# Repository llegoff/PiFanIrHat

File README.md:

[:fr:](LISEZMOI.md) [:uk:](README.md)

buy rev1 on [ebay](https://www.ebay.fr/itm/153597547428) :package:

buy rev1 (silent fan) on [ebay](https://www.ebay.fr/itm/153600642463) :package:

# PiFanIrHat

### Fan

:warning: need raspbian buster, good version of gpio-fan overlay, come with kernel 4.19.

configuration: edit /boot/config.txt, add folowing line

    dtoverlay=gpio-fan,gpiopin=18,temp=55000

### On/Off button

on/off button is connected to gpio3 and GND

configuration: edit /boot/config.txt, add folowing line

    dtoverlay=gpio-shutdown,gpio_pin=3,active_low=1,gpio_pull=up
    
:warning: on raspberry pi 4, only shutdown work, with original bootloader. For power on, bootloader need to be update to ~~RC3.3~~ last version (see https://www.raspberrypi.org/forums/viewtopic.php?f=117&t=246027)

Download the last bootloader at recovery section https://www.raspberrypi.org/downloads/

### IR receiver

install ir-keytable

    sudo apt install ir-keytable

configuration: edit /boot/config.txt, add folowing line

    dtoverlay=gpio-ir,gpio_pin=17,gpio_pull=1,rc-map-name=<keymap file for your remote>

keymap files path is /lib//udev/rc_keymaps/

test remote

    sudo ir-keytable -t -v -p all

### IR power On

:warning: on raspberry pi 4, only shutdown work, with original bootloader. For power on, bootloader need to be update to ~~RC3.3~~ last version (see https://www.raspberrypi.org/forums/viewtopic.php?f=117&t=246027)

Download the last bootloader at recovery section https://www.raspberrypi.org/downloads/

:grey_exclamation: For key learning, press Rec button, led stay on, press remote key, led return off.

flash Attiny85 with file [PiFanIr.hex](attiny85/PiFanIr.hex?raw=true)

    avrdude -p attiny85 -P COM5 -b 19200 -c avrisp -u -U flash:w:PiFanIr.hex

flash attiny85 fuses : lfuse:E2 , efuse:FF , hfuse:DF

    avrdude -p attiny85 -P COM5 -b 19200 -c avrisp -u -U lfuse:w:0xe2:m -U hfuse:w:0xdf:m -U efuse:w:0xff:m

## PCB

## Schematic

## Révision
rev1
- bad footprint for eeprom

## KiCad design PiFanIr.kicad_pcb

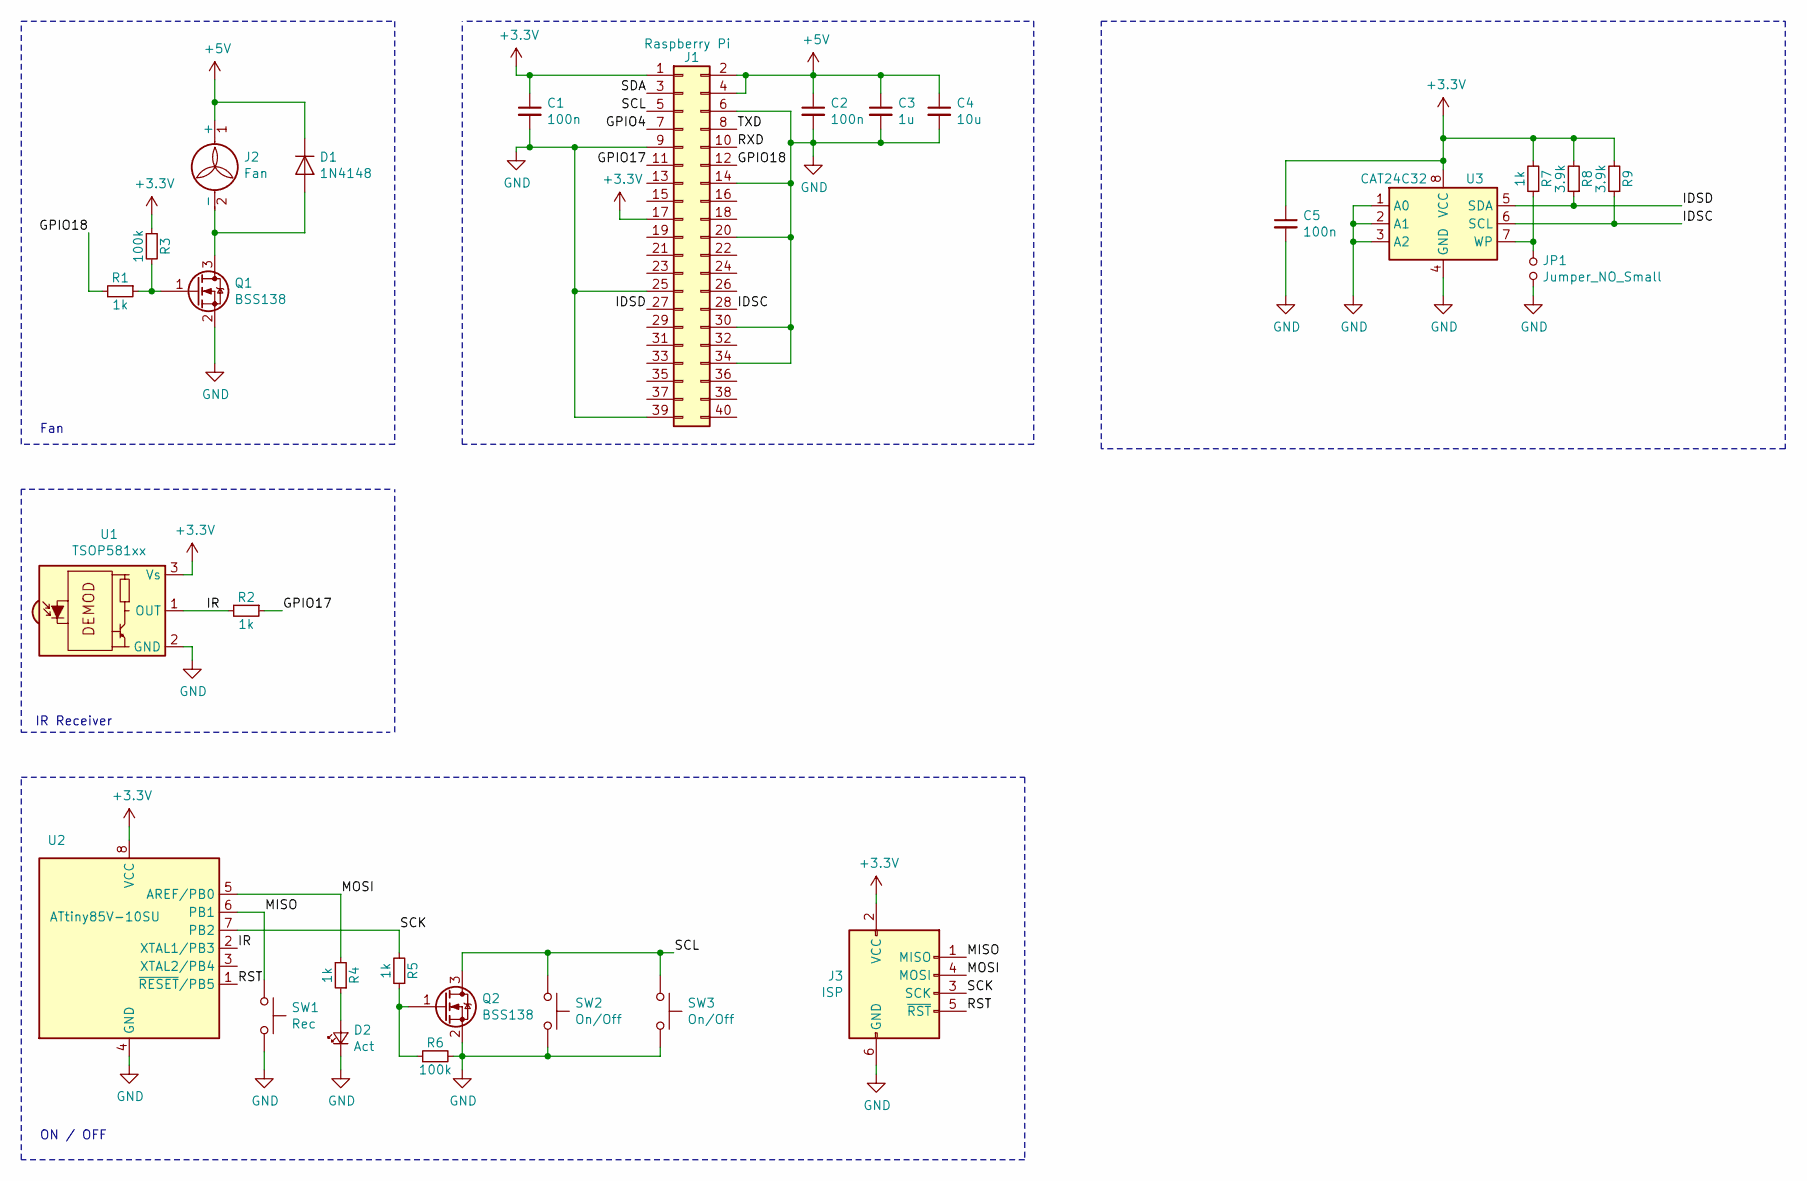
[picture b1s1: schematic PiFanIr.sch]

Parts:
C1, C2, C5: 100n; C_0805
C3: 1u; C_0805
C4: 10u; C_0805
D1: 1N4148; D_SOD-123
D2: Act; LED_0805
J1: Raspberry Pi; RaspberryPiHAT
J2: Fan; Pin_Header_Angled_1x02_Pitch2.54mm
J3: ISP; Pin_Header_Straight_2x03_Pitch2.54mm
JP1: Jumper_NO_Small; Pin_Header_Straight_1x02_Pitch2.54mm
Q1, Q2: BSS138; SOT-23
R1, R2, R4, R5, R7: 1k; R_0805
R3, R6: 100k; R_0805
R8, R9: 3.9k; R_0805
SW1: Rec; SW_SPST_TL3342
SW2: On/Off; SW_Tactile_SPST_Angled_PTS645Vx31-2LFS
SW3: On/Off; SW_SPST_TL3342
U1: TSOP581xx; IRReceiver_Vishay_MINICAST-3pin
U2: ATtiny85V-10SU; SOIJ-8_5.3x5.3mm_Pitch1.27mm
U3: CAT24C32; SOIJ-8_5.3x5.3mm_Pitch1.27mm

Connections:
+3V3: C1.1, C5.1, J1.1, J1.17, J3.2 (VCC), R3.1, R7.2, R8.2, R9.2, U1.3 (Vs), U2.8 (VCC), U3.8 (VCC)
+5V: C2.1, C3.1, C4.1, D1.1 (K), J1.2, J1.4, J2.1 (+)
/GPIO4: J1.7
/GPIO17: J1.11, R2.1
/GPIO18: J1.12, R1.2
/IDSC: J1.28, R9.1, U3.6 (SCL)
/IDSD: J1.27, R8.1, U3.5 (SDA)
/IR: R2.2, U1.1 (OUT), U2.2 (XTAL1/PB3)
/MISO: J3.1 (MISO), SW1.1, U2.6 (PB1)
/MOSI: J3.4 (MOSI), R4.2, U2.5 (AREF/PB0)
/RST: J3.5 (~RST), U2.1 (~RESET~/PB5)
/RXD: J1.10
/SCK: J3.3 (SCK), R5.2, U2.7 (PB2)
/SCL: J1.5, Q2.3 (D), SW2.1, SW3.1
/SDA: J1.3
/TXD: J1.8
GND: C1.2, C2.2, C3.2, C4.2, C5.2, D2.1 (K), J1.6, J1.9, J1.14, J1.20, J1.25, J1.30, J1.34, J1.39, J3.6 (GND), JP1.2, Q1.2 (S), Q2.2 (S), R6.2, SW1.2, SW2.2, SW3.2, U1.2 (GND), U2.4 (GND), U3.1 (A0), U3.2 (A1), U3.3 (A2), U3.4 (GND)
unnamed: D1.2 (A), J2.2 (-), Q1.3 (D)
unnamed: D2.2 (A), R4.1
unnamed: JP1.1, R7.1, U3.7 (WP)
unnamed: Q1.1 (G), R1.1, R3.2
unnamed: Q2.1 (G), R5.1, R6.1

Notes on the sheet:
Fan
IR Receiver
ON / OFF

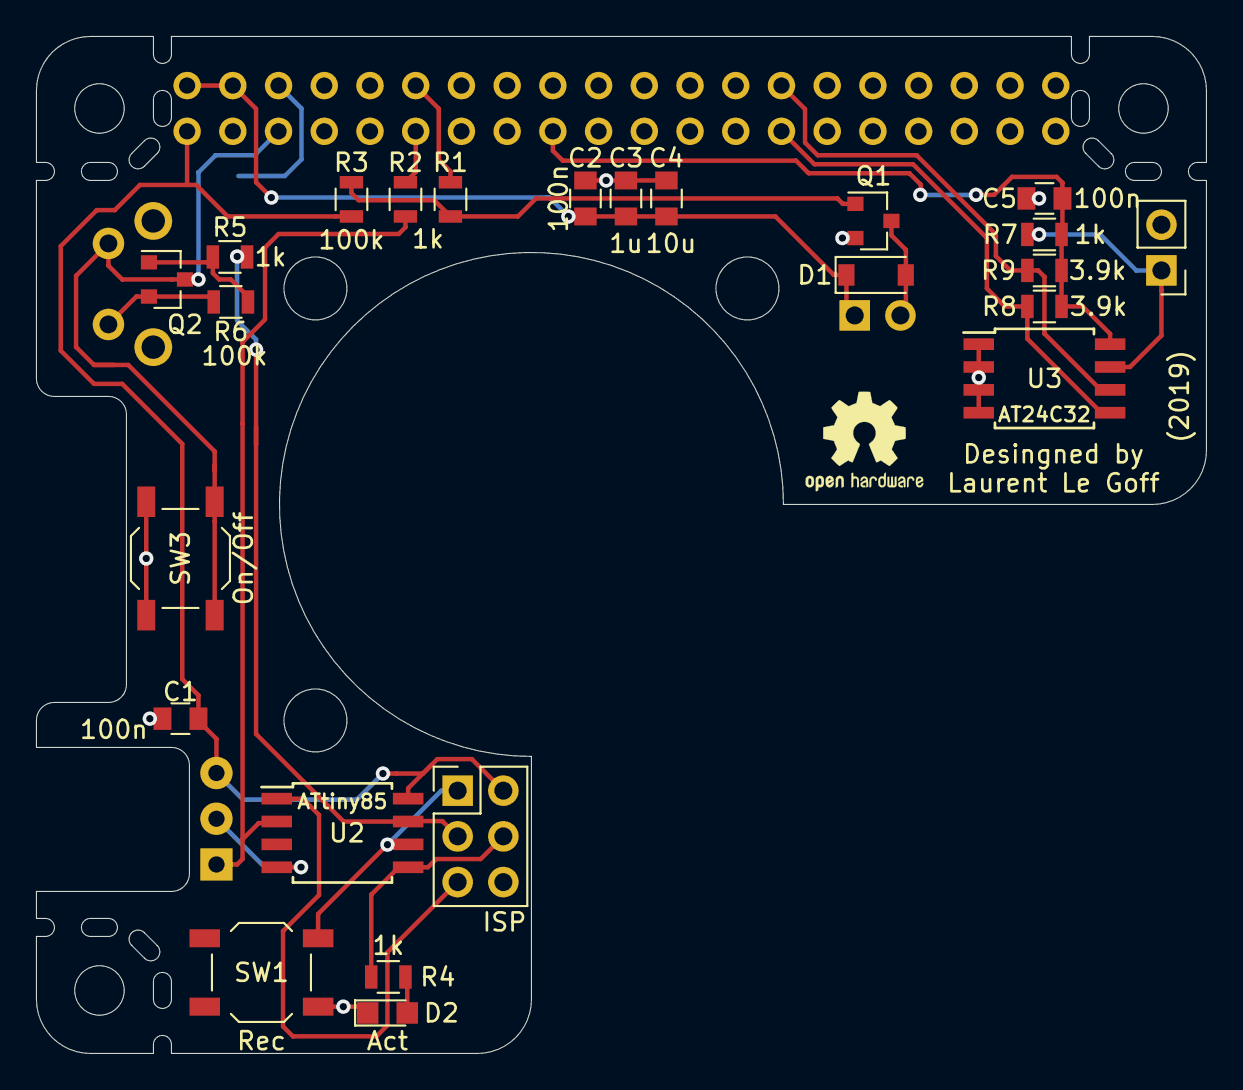
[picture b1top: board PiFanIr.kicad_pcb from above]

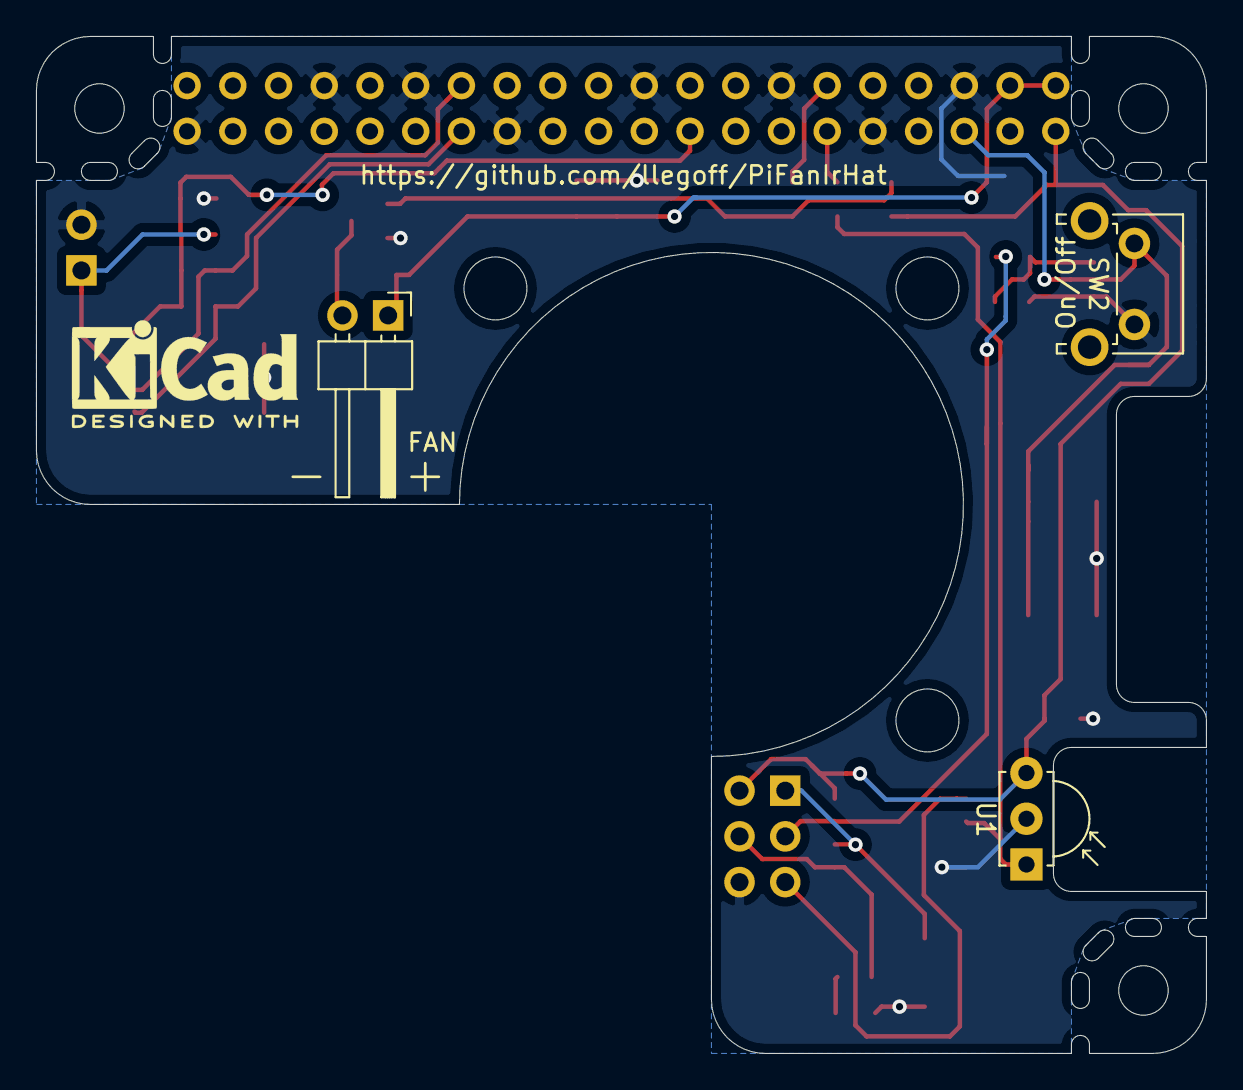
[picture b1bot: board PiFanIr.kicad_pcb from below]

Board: 2 copper layers, 65.0 x 56.5 mm, 28 parts (3 on the bottom side), 18 nets.
